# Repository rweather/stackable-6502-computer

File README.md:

Stackable 6502 Computer
=======================

This repository contains schematics, PCB layouts, and other information
for a "stackable" design for a 6502-based computer based on
[Ben Eater's Breadboard 6502 Computer](https://eater.net/6502) with
options to expand with daughter boards (or "shields" in the Arduino sense).

The CPU, memory, VIA, and address decoding are on the base board with pin
headers to connect to other boards:

Here is the Stackable 6502 Computer with the I/O board fitted:

Other boards are possible in the future; see **Future Expansion Ideas** below.

Repository Layout
-----------------

* `kicad` - Schematics and PCB layouts in [KiCad format](https://www.kicad.org/).
* `kicad/BaseBoard` - Base board schematic and layout (4-layer).
* `kicad/IoBoard` - I/O board schematic and layout (2-layer).
* `kicad/Library` - Library of common schematic symbols and footprints.
* `schematics` - PDF versions of the schematics.
* `gerber` - Gerber files for all of the boards.
* `roms` - ROM images for test programs.
* `src` - Source code for test programs.

Schematics and Parts
--------------------

PDF versions of the schematics are available for the
[Base Board](schematics/BaseBoard.pdf) and [I/O Board](schematics/IoBoard.pdf)
in the `schematics` subdirectory.  The `gerber` directory contains the
Gerber files if you want to get your own PCB's made.

I used [PCBway](https://www.pcbway.com/) for my PCB's.  The PCB's for
the base board and I/O board are 4-layer boards.  You can order your
own PCB's from PCBway here:

* [Base Board](https://www.pcbway.com/project/shareproject/W132188ASZ13_Stackable_6502_BaseBoard_01ef6257.html)
* [I/O Board](https://www.pcbway.com/project/shareproject/W132188ASZ14_Stackable_6502_IoBoard_ac81ba96.html)

The parts list for this project can be found in the file
[Parts.md](doc/Parts.md) in the `doc` subdirectory.  There are some
alternatives on how you can build it, so some parts are optional:

* The 1MHz crystal oscillator can use either the 14-pin DIP style package (X1)
or the 8-pin DIP style package (X2) version.  Fit only one of the oscillators.
* Address decoding can use either a simple 74LS00 NAND gate, or a
ATF22V10C-7PX Programmable Logic Device (PLD).  It is easiest to start with
the NAND gate, but the PLD provides a lot of flexibility in memory layout.
* Optional 3.3V power supply using a L78L33 3.3V voltage regulator.
This will be handy if you plan to interface to 3.3V equipment using
level conversion.
* MCP3208 12-bit SPI ADC on the I/O board for reading analog inputs.

I suggest studying the schematics and the build instructions before
deciding which options you need.

Base Board
----------

The 156mm x 82mm base board was based on the design for
[Ben Eater's Breadboard 6502 Computer](https://eater.net/6502) with some
modifications to help with expandability:

* W65C02S or pin-compatible microprocessor.
* 62256 32K x 8 static RAM.
* 28C256 32K x 8 EEPROM, mounted in a 28-pin ZIF socket at the end of the
  base board to give clearance between the socket and daughter boards.
  A regular 28-pin socket can be used instead of the ZIF if you prefer.
* 6522 Versatile Interface Adapter (VIA).
* Address decoding logic using either a 74LS00 quad NAND gate as in Ben Eater's
  original design, or a ATF22V10C-7PX programmable logic device (PLD).
* 5V and 3.3V power supplies based on a 9-12V DC input.
* Pin headers to expose power, bus lines, and control lines to the
  attached daughter boards.
* 4-layer PCB with ground and 5V on the two inner layers.

The pin headers are aligned on a strict 2.54mm (0.1 inch) grid to allow
standard 120mm x 80mm stripboard or protoboard to be used when creating
daughter board "shields".

If you want to lay out your own shield PCB, then you can use the
`Stackable6502Shield` symbol and footprint from `kicad/Library`
as a starting point.

See [Build-Base-Board.md](doc/Build-Base-Board.md) in the `doc`
subdirectory for instructions on building the base board.

I/O Board
---------

The 125 x 82mm I/O board provides the following features:

* RS-232 serial interface using the 6551 ACIA, with RTS handshaking.
* SPI bus interface, connected to the 6522 VIA on the base board.
* SD card interface, connected to the SPI bus interface.
* 8 analog inputs using the MCP3208 12-bit SPI ADC chip.
* "PWM" header for square wave output on PB7 of the 6522 VIA.
  A piezo-buzzer can be connected to the header for making simple sounds.
* Provision for 3mm LED's on PB0..PB3 for indication.

As can be seen, the I/O board is very featureful.  Not all features need
to be fitted at once.  You can customise it for your requirements.

See [Build-Io-Board.md](doc/Build-Io-Board.md) in the `doc`
subdirectory for instructions on building the I/O board.

Future Expansion Ideas
----------------------

I'd like to design a memory expansion board with large amounts of
bank-switched RAM.  The ATF22V10C-7PX PLD can help with this, redirecting
memory requests away from the standard RAM to the additional banks.

SPI-based NAND or NOR flash chip for long term storage.  The contents of
flash could be loaded into the bank-switched RAM at startup to provide
ROM replacement capabilities.

An interface to an SPI-based Arduino LCD or OLED module may be interesting.

An alternative serial interface using a FTDI chip for serial over USB.

Address Decoding
----------------

The 74LS00 quad NAND gate on the base board implements the same memory
map as Ben Eater's original design:

* `0x0000 - 0x3FFF` - 16K of static RAM
* `0x4000 - 0x4FFF` - Unused
* `0x5000 - 0x5FFF` - ACIA
* `0x6000 - 0x6FFF` - VIA
* `0x7000 - 0x7FFF` - Do not use due to conflicts between the ACIA and VIA
* `0x8000 - 0xFFFF` - 32K of EEPROM

This arrangement is very wasteful of address space, particularly the
static RAM, but is very simple.  More complex arrangements require more
logic gates.

The ATF22V10C-7PX PLD provides greater flexibility in allocating address
ranges.  The PLD can be programmed to allocate the memory map in almost
any way, and to provide additional chip select outputs for devices on
daughter boards.  Addresses can be mapped with 64-byte granularity.

Note: I am still working on the PLD code.  More later.

License
-------

<p xmlns:cc="http://creativecommons.org/ns#" xmlns:dct="http://purl.org/dc/terms/"><span property="dct:title">Stackable 6502 Computer</span> by <span property="cc:attributionName">Rhys Weatherley</span> is licensed under <a href="http://creativecommons.org/licenses/by-nc-sa/4.0/?ref=chooser-v1" target="_blank" rel="license noopener noreferrer" style="display:inline-block;">Attribution-NonCommercial-ShareAlike 4.0 International</a></p>

Contact
-------

For more information on this project, to report bugs, or to suggest
improvements, please contact the author Rhys Weatherley via
[email](mailto:rhys.weatherley@gmail.com).

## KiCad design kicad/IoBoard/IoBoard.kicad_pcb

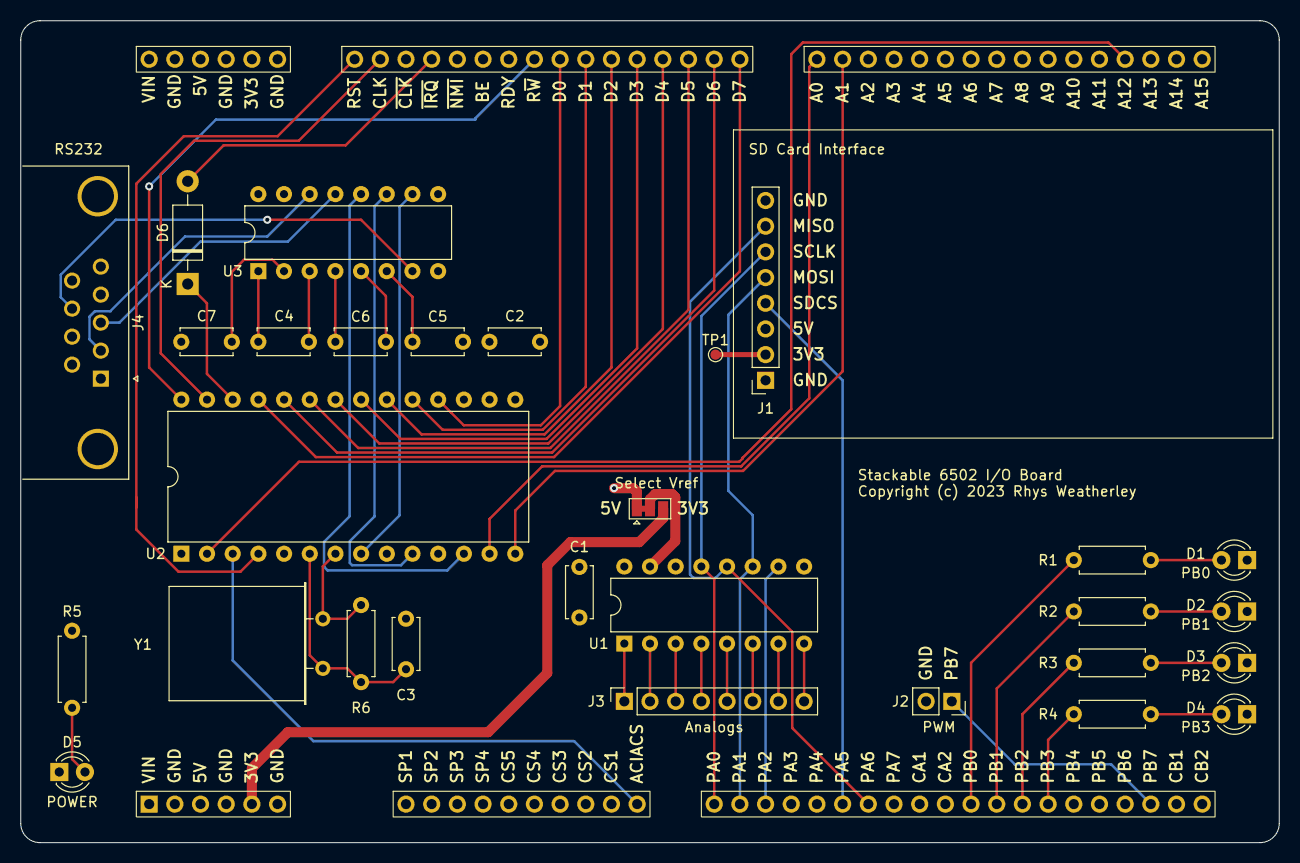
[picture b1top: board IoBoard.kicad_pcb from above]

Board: 4 copper layers, 124.5 x 81.3 mm, 30 parts (0 on the bottom side), 60 nets.

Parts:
A1: Shield; Stackable6502Shield
C1, C2: 100nF; C_Disc_D5.0mm_W2.5mm_P5.00mm
C3: 20pF; C_Disc_D5.0mm_W2.5mm_P5.00mm
C4, C5, C6, C7: 1uF; C_Disc_D5.0mm_W2.5mm_P5.00mm
D1: PB0; LED_D3.0mm
D2: PB1; LED_D3.0mm
D3: PB2; LED_D3.0mm
D4: PB3; LED_D3.0mm
D5: POWER; LED_D3.0mm
D6: SB140; D_DO-41_SOD81_P10.16mm_Horizontal
J1: SD Card Interface; PinSocket_1x08_P2.54mm_Vertical
J2: PWM; PinSocket_1x02_P2.54mm_Vertical
J3: Analogs; PinSocket_1x08_P2.54mm_Vertical
J4: RS232; DSUB-9_Female_Horizontal_P2.77x2.84mm_EdgePinOffset4.94mm_H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
JP1: Select Vref; SolderJumper-3_P1.3mm_Bridged12_Pad1.0x1.5mm
R1, R2, R3, R4, R5: 1K; R_Axial_DIN0207_L6.3mm_D2.5mm_P7.62mm_Horizontal
R6: 1M; R_Axial_DIN0207_L6.3mm_D2.5mm_P7.62mm_Horizontal
TP1: SD 3.3V Output; TestPoint_Pad_D1.0mm
U1: MCP3208; DIP-16_W7.62mm
U2: W65C51NxP; DIP-28_W15.24mm
U3: MAX232; DIP-16_W7.62mm
Y1: 1.8432MHz; Crystal_HC49-U_Horizontal

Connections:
+3V3: A1.5 (3V3), A1.70 (3V3), JP1.3 (B)
+5V: A1.3 (5V), A1.72 (5V), C1.1, C2.1, J1.3, JP1.1 (A), R5.1, U1.16 (Vdd), U2.15 (VCC), U3.16 (VCC)
ACIACS: A1.16 (ACIACS), U2.3 (~CS2)
ADCCS: A1.19 (PA2), U1.10 (~CS/SHDN)
CLK: A1.67 (CLK), U2.27 (ϕ2)
GND: A1.2 (GND), A1.4 (GND), A1.6 (GND), A1.69 (GND), A1.71 (GND), A1.73 (GND), C1.2, C2.2, C3.2, C5.2, C7.2, D1.1 (K), D2.1 (K), D3.1 (K), D4.1 (K), D5.1 (K), J1.1, J1.8, J2.2, J4.5, U1.9 (DGND), U1.14 (AGND), U2.1 (VSS), U2.9 (~CTS), U2.16 (~DCD), U2.17 (~DSR), U3.15 (GND)
IRQ: A1.65 (~IRQ), D6.2 (A)
MISO: A1.23 (PA6), J1.7, U1.12 (Dout)
MOSI: A1.18 (PA1), J1.5, U1.11 (Din)
unnamed: D1.2 (A), R1.2
unnamed: D2.2 (A), R2.2
unnamed: D3.2 (A), R3.2
unnamed: D4.2 (A), R4.2
unnamed: D5.2 (A), R5.2
unnamed: D6.1 (K), U2.26 (~IRQ)
unnamed: J1.2, TP1.1
unnamed: J3.1, U1.1 (CH0)
unnamed: J3.2, U1.2 (CH1)
unnamed: J3.3, U1.3 (CH2)
unnamed: J3.4, U1.4 (CH3)
unnamed: J3.5, U1.5 (CH4)
unnamed: J3.6, U1.6 (CH5)
unnamed: J3.7, U1.7 (CH6)
unnamed: J3.8, U1.8 (CH7)
unnamed: JP1.2 (C), U1.15 (Vref)
unnamed: U2.12 (RxD), U3.12 (R1OUT)
unnamed: U2.10 (TxD), U3.11 (T1IN)
unnamed: C3.1, R6.1, U2.6 (XTAL1), Y1.2
unnamed: R6.2, U2.7 (XTAL2), Y1.1
unnamed: U2.8 (~RTS), U3.10 (T2IN)
unnamed: C4.1, U3.1 (C1+)
unnamed: C4.2, U3.3 (C1-)
unnamed: C6.1, U3.4 (C2+)
unnamed: C6.2, U3.5 (C2-)
unnamed: J4.3, U3.13 (R1IN)
unnamed: J4.2, U3.14 (T1OUT)
unnamed: J4.8, U3.7 (T2OUT)
unnamed: C7.1, U3.2 (VS+)
unnamed: C5.1, U3.6 (VS-)
RESET: A1.68 (RST), U2.4 (~RES)
RW: A1.61 (R~W), U2.28 (R/~W)
SCLK: A1.17 (PA0), J1.6, U1.13 (CLK)
SDCS: A1.22 (PA5), J1.4
VDD: A1.1 (VIN), A1.74 (VIN)
a0: A1.52 (A0), U2.13 (RS0)
a1: A1.51 (A1), U2.14 (RS1)
a12: A1.40 (A12), U2.2 (CS1)
d0: A1.60 (D0), U2.18 (D0)
d1: A1.59 (D1), U2.19 (D1)
d2: A1.58 (D2), U2.20 (D2)
d3: A1.57 (D3), U2.21 (D3)
d4: A1.56 (D4), U2.22 (D4)
d5: A1.55 (D5), U2.23 (D5)
d6: A1.54 (D6), U2.24 (D6)
d7: A1.53 (D7), U2.25 (D7)
q0: A1.27 (PB0), R1.1
q1: A1.28 (PB1), R2.1
q2: A1.29 (PB2), R3.1
q3: A1.30 (PB3), R4.1
q7: A1.34 (PB7), J2.1

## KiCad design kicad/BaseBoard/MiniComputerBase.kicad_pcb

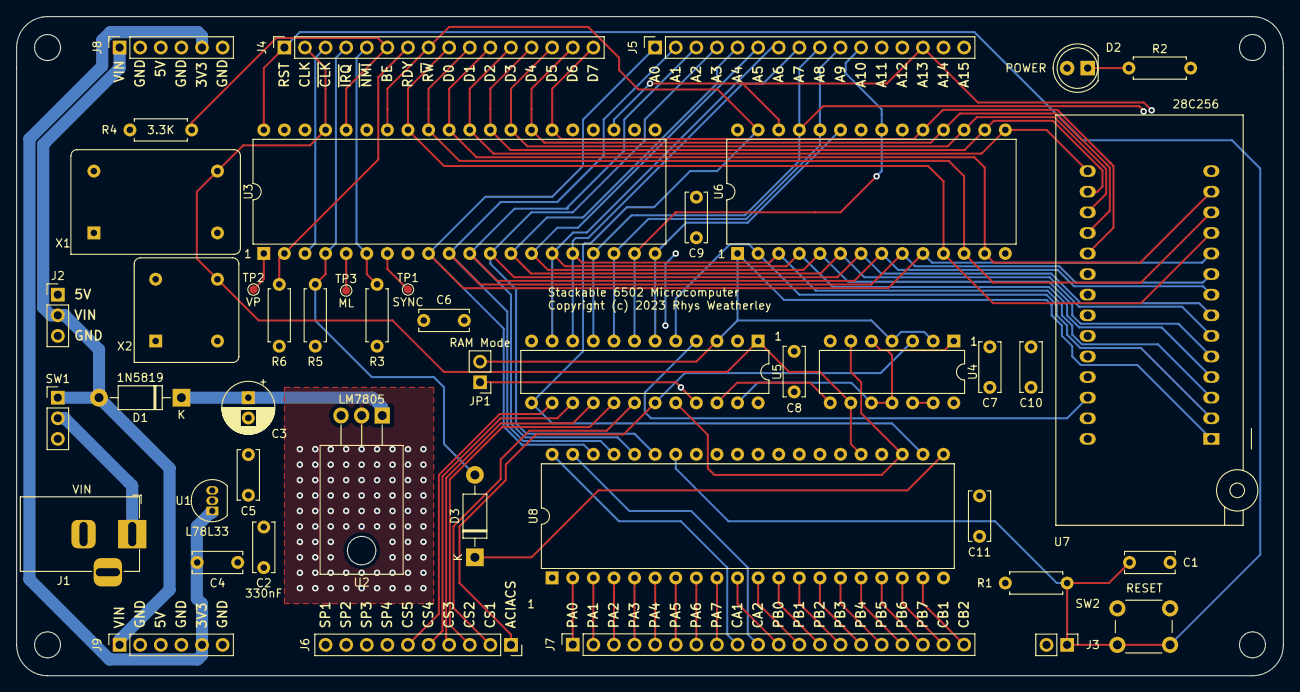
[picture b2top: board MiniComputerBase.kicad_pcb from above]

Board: 4 copper layers, 156.2 x 81.3 mm, 49 parts (0 on the bottom side), 73 nets.

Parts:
C1, C4, C5, C6, C7, C8, C9, C10, C11: 100nF; C_Disc_D6.0mm_W2.5mm_P5.00mm
C2: 330nF; C_Disc_D6.0mm_W2.5mm_P5.00mm
C3: 47uF; CP_Radial_D6.3mm_P2.50mm
D1: 1N5819; D_DO-41_SOD81_P10.16mm_Horizontal
D2: POWER; LED_D5.0mm
D3: SB140; D_DO-41_SOD81_P10.16mm_Horizontal
H1: Hole1; MountingHole_3.2mm_M3
H2: Hole2; MountingHole_3.2mm_M3
H3: Hole3; MountingHole_3.2mm_M3
H4: Hole4; MountingHole_3.2mm_M3
J1: VIN; BarrelJack_Horizontal
J2: PWRALT; PinHeader_1x03_P2.54mm_Vertical
J3: RESET; PinHeader_1x02_P2.54mm_Vertical
J4: Control and Data; PinSocket_1x16_P2.54mm_Vertical
J5: Address Bus; PinSocket_1x16_P2.54mm_Vertical
J6: Chip Selects; PinSocket_1x10_P2.54mm_Vertical
J7: PA/PB; PinSocket_1x20_P2.54mm_Vertical
J8, J9: Power; PinSocket_1x06_P2.54mm_Vertical
JP1: RAM Mode; PinHeader_1x02_P2.54mm_Vertical
R1: 1K; R_Axial_DIN0207_L6.3mm_D2.5mm_P7.62mm_Horizontal
R2: 220R; R_Axial_DIN0207_L6.3mm_D2.5mm_P7.62mm_Horizontal
R3, R5: 10K; R_Axial_DIN0207_L6.3mm_D2.5mm_P7.62mm_Horizontal
R4, R6: 3.3K; R_Axial_DIN0207_L6.3mm_D2.5mm_P7.62mm_Horizontal
SW1: POWER; PinHeader_1x03_P2.54mm_Vertical
SW2: RESET; SW_PUSH_6mm_H5mm
TP1: SYNC; TestPoint_Pad_D1.0mm
TP2: VP; TestPoint_Pad_D1.0mm
TP3: ML; TestPoint_Pad_D1.0mm
U1: L78L33; TO-92_Inline
U2: LM7805; TO-220-3_Horizontal_TabDown
U3: W65C02SxP; DIP-40_W15.24mm
U4: 74LS00; DIP-14_W7.62mm
U5: ATF22V10C; DIP-24_W7.62mm
U6: 62256; DIP-28_W15.24mm
U7: 28C256; DIP_Socket-28_W11.9_W12.7_W15.24_W17.78_W18.5_3M_228-1277-0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
U8: W65C22NxP; DIP-40_W15.24mm
X1: XTAL; Oscillator_DIP-14
X2: XTAL_ALT; Oscillator_DIP-8

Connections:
+3V3: C4.1, J8.5, J9.5, U1.1 (VO)
+5V: C2.1, C5.1, C6.1, C7.1, C8.1, C9.1, C10.1, C11.1, D2.2 (A), J2.1, J8.3, J9.3, R1.1, R3.1, R4.1, R5.1, R6.1, U1.3 (VI), U2.3 (OUT), U3.8 (VDD), U3.38 (~SO), U4.14 (VCC), U5.24 (VCC), U6.28 (VCC), U7.27 (~WE), U7.28 (VCC), U8.20 (VCC), X1.14 (Vcc), X2.8 (Vcc)
ACIACS: J6.1, U4.3, U5.19 (IO19)
BE: J4.6, R4.2, U3.36 (BE)
CLK: J4.2, U3.37 (ϕ0), U4.9, U5.1 (CLKIN1), U8.25 (ϕ2), X1.8 (OUT), X2.5 (OUT)
GND: C1.2, C2.2, C3.2, C4.2, C5.2, C6.2, C7.2, C8.2, C9.2, C10.2, C11.2, J1.2, J2.3, J3.2, J8.2, J8.4, J8.6, J9.2, J9.4, J9.6, R2.2, SW2.1, U1.2 (GND), U2.2 (GND), U3.21 (VSS), U4.7 (GND), U5.12 (GND), U6.14 (GND), U7.14 (GND), U7.22 (~OE), U8.1 (VSS), X1.7 (GND), X2.4 (GND)
IOCS1: J6.2, U5.18 (IO18)
IOCS2: J6.3, U5.17 (IO17)
IOCS3: J6.4, U5.16 (IO16)
IOCS4: J6.5, U5.15 (IO15)
IOCS5: J6.6, U5.14 (IO14)
IRQ: D3.2 (A), J4.4, R5.2, U3.4 (~IRQ)
NMI: J4.5, R3.2, U3.6 (~NMI)
unnamed: C3.1, D1.1 (K), U2.1 (IN)
unnamed: D2.1 (K), R2.1
unnamed: D3.1 (K), U8.21 (~IRQ)
unnamed: J7.1, U8.2 (PA0)
unnamed: J7.2, U8.3 (PA1)
unnamed: J7.3, U8.4 (PA2)
unnamed: J7.4, U8.5 (PA3)
unnamed: J7.5, U8.6 (PA4)
unnamed: J7.6, U8.7 (PA5)
unnamed: J7.7, U8.8 (PA6)
unnamed: J7.8, U8.9 (PA7)
unnamed: J7.9, U8.40 (CA1)
unnamed: J7.10, U8.39 (CA2)
unnamed: J7.11, U8.10 (PB0)
unnamed: J7.12, U8.11 (PB1)
unnamed: J7.13, U8.12 (PB2)
unnamed: J7.14, U8.13 (PB3)
unnamed: J7.15, U8.14 (PB4)
unnamed: J7.16, U8.15 (PB5)
unnamed: J7.17, U8.16 (PB6)
unnamed: J7.18, U8.17 (PB7)
unnamed: J7.19, U8.18 (CB1)
unnamed: J7.20, U8.19 (CB2)
unnamed: J1.1, SW1.2 (B)
unnamed: TP1.1, U3.7 (SYNC)
unnamed: TP3.1, U3.5 (~ML)
unnamed: TP2.1, U3.1 (~VP)
RAMCS: U4.8, U5.22 (IO22), U6.20 (~CS)
RAMOE: JP1.1 (A), U5.21 (IO21), U6.22 (~OE)
RDY: J4.7, R6.2, U3.2 (RDY)
RESET: C1.1, J3.1, J4.1, R1.2, SW2.2, U3.40 (~RES), U8.34 (~RES)
ROMCS: U4.1, U4.5, U4.10, U4.11, U5.23 (IO23), U7.20 (~CS)
RW: J4.8, U3.34 (R/~W), U5.13 (IN13), U6.27 (~WE), U8.22 (R/~W)
VDD: D1.2 (A), J2.2, J8.1, J9.1, SW1.1 (A)
VIACS: U4.6, U5.20 (IO20), U8.23 (~CS2)
a0: J5.1, U3.9 (A0), U6.10 (A0), U7.10 (A0), U8.38 (RS0)
a1: J5.2, U3.10 (A1), U6.9 (A1), U7.9 (A1), U8.37 (RS1)
a2: J5.3, U3.11 (A2), U6.8 (A2), U7.8 (A2), U8.36 (RS2)
a3: J5.4, U3.12 (A3), U6.7 (A3), U7.7 (A3), U8.35 (RS3)
a4: J5.5, U3.13 (A4), U6.6 (A4), U7.6 (A4)
a5: J5.6, U3.14 (A5), U6.5 (A5), U7.5 (A5)
a6: J5.7, U3.15 (A6), U5.11 (IN11), U6.4 (A6), U7.4 (A6)
a7: J5.8, U3.16 (A7), U5.10 (IN10), U6.3 (A7), U7.3 (A7)
a8: J5.9, U3.17 (A8), U5.9 (IN9), U6.25 (A8), U7.25 (A8)
a9: J5.10, U3.18 (A9), U5.8 (IN8), U6.24 (A9), U7.24 (A9)
a10: J5.11, U3.19 (A10), U5.7 (IN7), U6.21 (A10), U7.21 (A10)
a11: J5.12, U3.20 (A11), U5.6 (IN6), U6.23 (A11), U7.23 (A11)
a12: J5.13, U3.22 (A12), U5.5 (IN5), U6.2 (A12), U7.2 (A12)
a13: J5.14, U3.23 (A13), U5.4 (IN4), U6.26 (A13), U7.26 (A13), U8.24 (CS1)
a14: J5.15, JP1.2 (B), U3.24 (A14), U4.2, U4.4, U5.3 (IN3), U6.1 (A14), U7.1 (A14)
a15: J5.16, U3.25 (A15), U4.12, U4.13, U5.2 (IN2)
d0: J4.9, U3.33 (D0), U6.11 (Q0), U7.11 (D0), U8.33 (D0)
d1: J4.10, U3.32 (D1), U6.12 (Q1), U7.12 (D1), U8.32 (D1)
d2: J4.11, U3.31 (D2), U6.13 (Q2), U7.13 (D2), U8.31 (D2)
d3: J4.12, U3.30 (D3), U6.15 (Q3), U7.15 (D3), U8.30 (D3)
d4: J4.13, U3.29 (D4), U6.16 (Q4), U7.16 (D4), U8.29 (D4)
d5: J4.14, U3.28 (D5), U6.17 (Q5), U7.17 (D5), U8.28 (D5)
d6: J4.15, U3.27 (D6), U6.18 (Q6), U7.18 (D6), U8.27 (D6)
d7: J4.16, U3.26 (D7), U6.19 (Q7), U7.19 (D7), U8.26 (D7)
nCLK: J4.3, U3.3 (ϕ1)

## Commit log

2023-10-26 Base board schematic and layout
2023-11-11 I/O board schematic and layout
2023-11-11 Gerber files
2023-11-21 Documentation
2023-11-25 Component updates after first build
2023-11-25 Build instructions for the base board
2023-11-25 Add license and 3D rendering of base board
2023-11-26 Build instructions for the I/O board
2023-11-28 Power-on self test ROM for the device
2023-12-01 Music examples
2023-12-01 More build instructions
2023-12-01 Remove PLD info for now until I can get it to work
2023-12-01 Glory shots of the finished boards
2023-12-01 Fix markdown
2023-12-01 Add links to shared PCBway project pages
2023-12-04 Add links to PCBway on the Parts.md page
2024-10-17 Fix an error in the parts list

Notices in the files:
kicad/BaseBoard/MiniComputerBase.kicad_pcb:
Copyright (c) 2023 Rhys Weatherley
